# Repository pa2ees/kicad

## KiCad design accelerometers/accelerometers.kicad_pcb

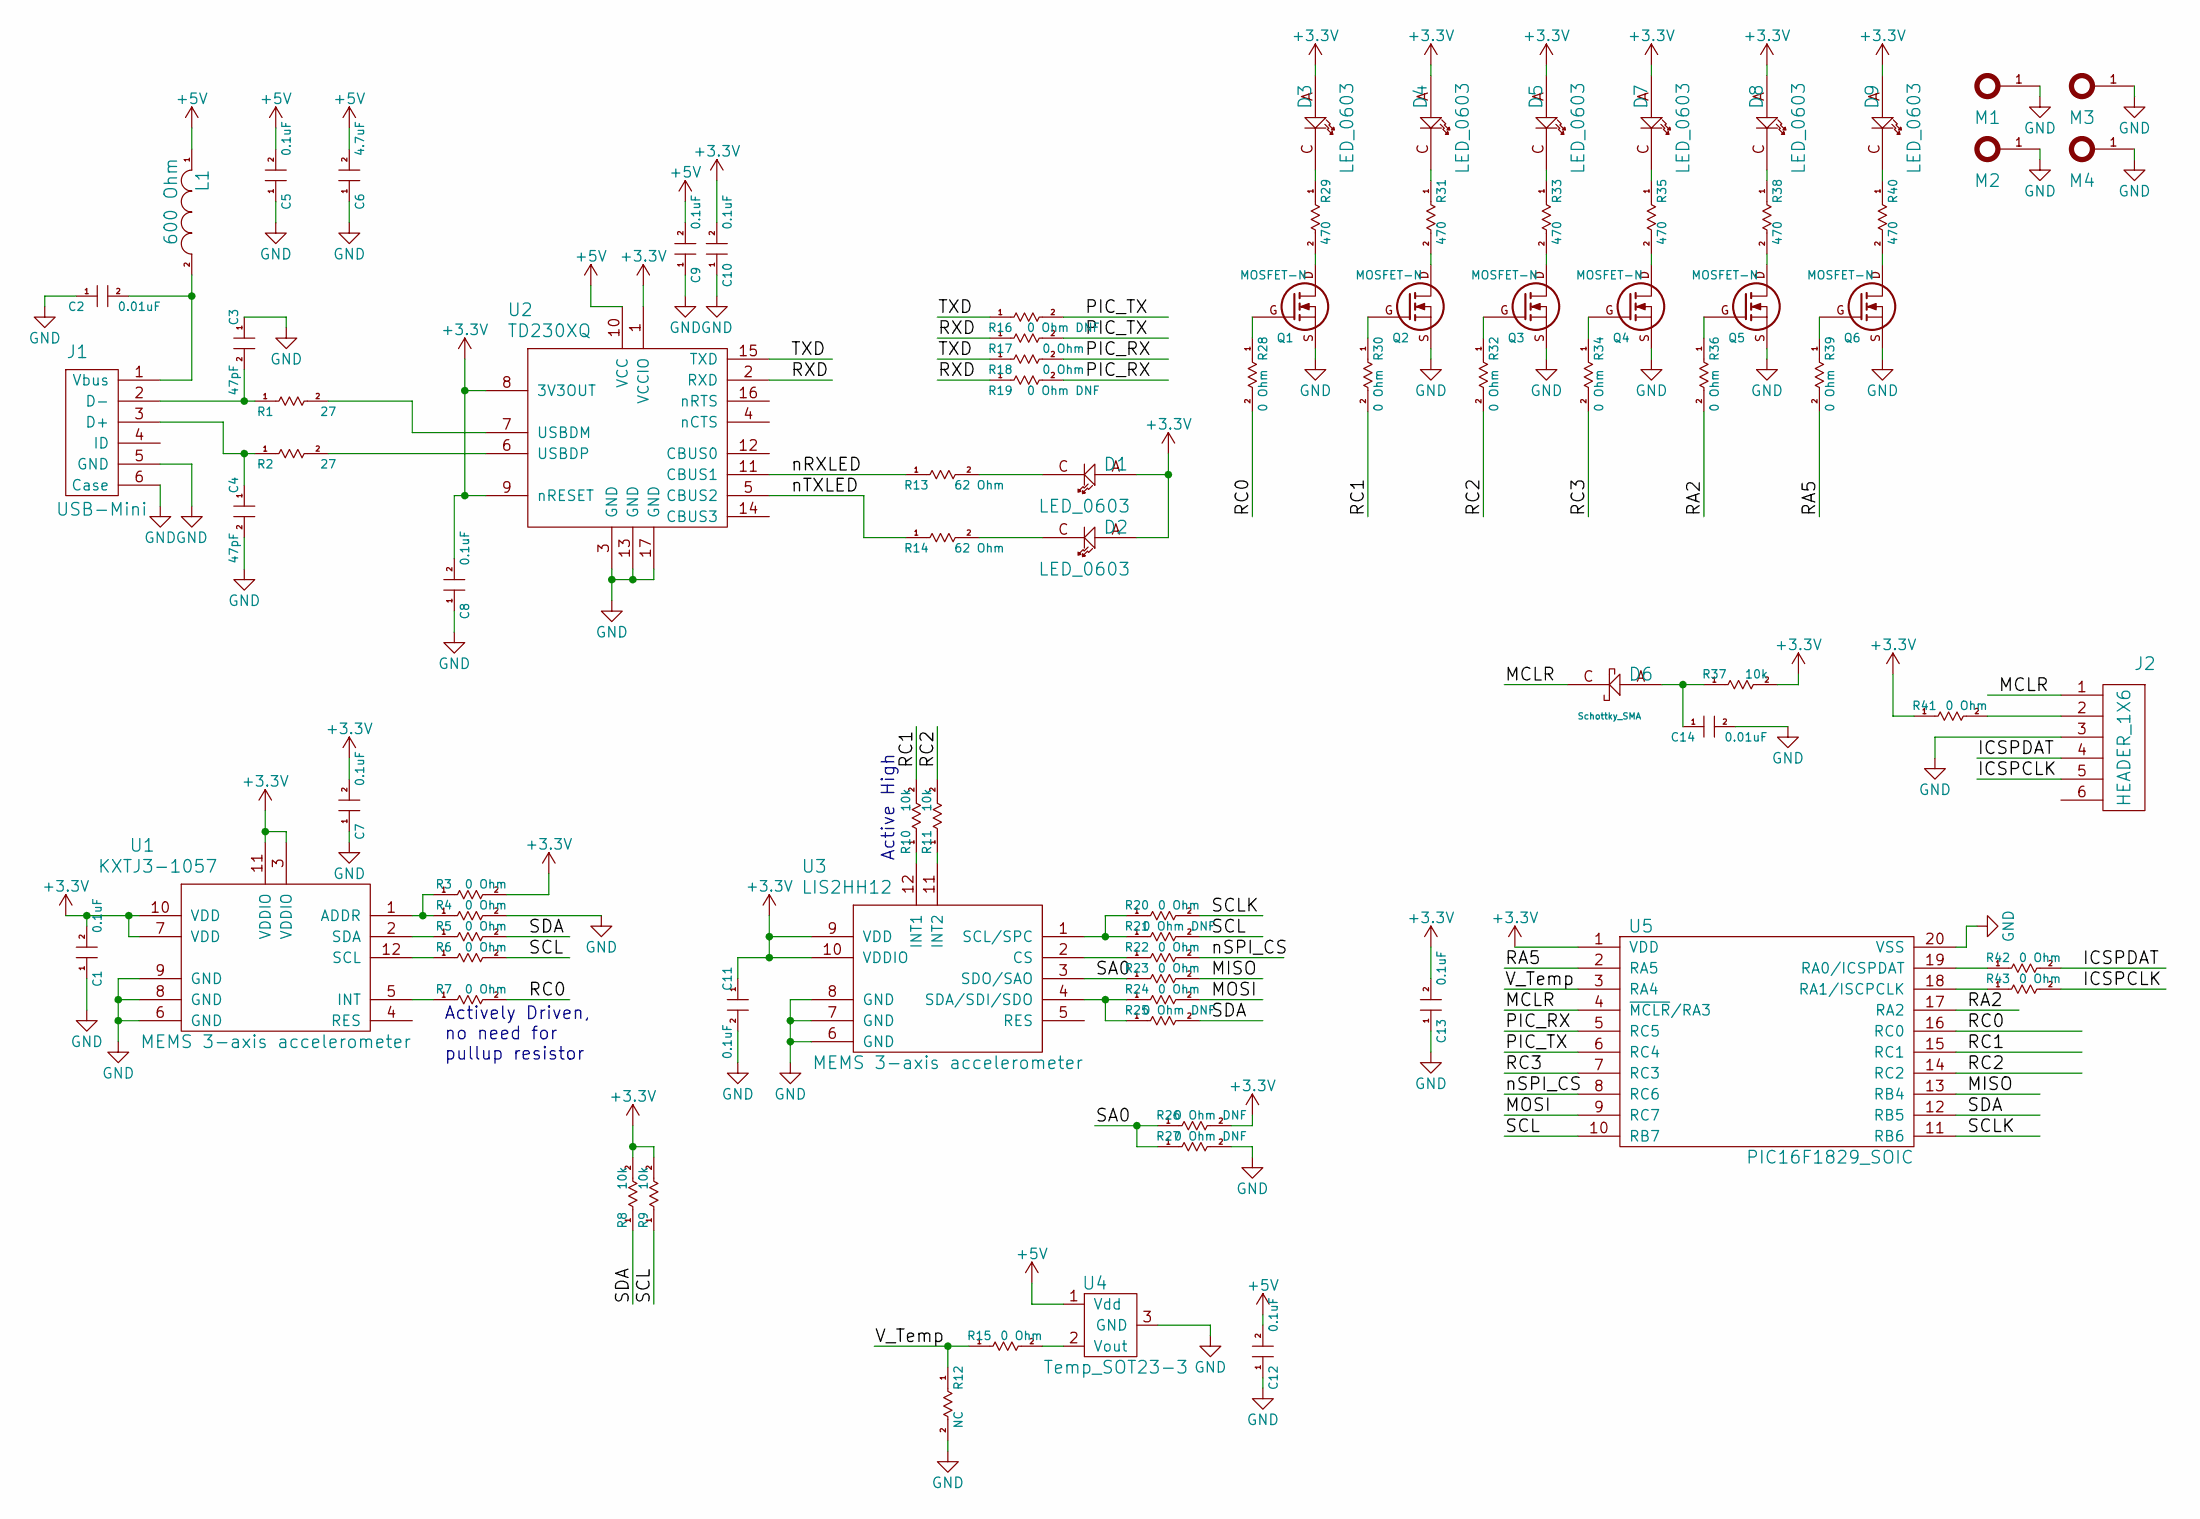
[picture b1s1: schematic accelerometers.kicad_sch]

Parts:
C1, C2, C3, C4, C5, C7, C8, C9, C10, C11: CAP_0603; C0603; MFG_PN {PN}
C6: CAP_0805; C0805; MFG_PN {PN}
C12, C13, C14: CAP_0603; C0603
D1, D2, D3, D4, D5, D7, D8, D9: LED_0603; D0603; MFG_PN LTST-C191KGKT
D6: Schottky_SMA; SMA; MFG_PN {PN}
J1: USB-Mini; MFG_PN 690-005-299-043
J2: HEADER_1X6; Header_6-pin_100mil
L1: IND; C0805; MFG_PN MI0805K601R-10
M1, M2, M3, M4: MNT-3MM; MNT-3mm
Q1, Q2, Q3, Q4, Q5, Q6: MOSFET-N; SOT-23-3-FET; MFG_PN 2N7002
R1, R2, R13, R14, R16, R17, R18, R19: RES_0603; R0603; MFG_PN {PN}
R3, R4, R5, R6, R7, R8, R9, R10, R11, R12, R15, R20, R21, R22, R23, R24, R25, R26, R27, R28, R30, R32, R34, R36, R37, R39, R41, R42, R43: RES_0603; R0603
R29, R31, R33, R35, R38, R40: RES_0603; R0603; MFG_PN RC0603JR-07470RL
U1: KXTJ3-1057; LGA12-2mm; MFG_PN KXTJ3-1057
U2: TD230XQ; QFN16-4mm; MFG_PN FT230XQ-R
U3: LIS2HH12; LGA12-2mm; MFG_PN LIS2HH12TR
U4: Temp_SOT23-3; SOT-23-3; MFG_PN MCP9700T
U5: PIC16F1829_SOIC; SO-20_300

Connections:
+3V3: C1.2, C7.2, C8.2, C10.2, C11.1, C13.2, D1.A, D2.A, D3.A, D4.A, D5.A, D7.A, D8.A, D9.A, R3.2, R8.2, R9.2, R26.2, R37.2, R41.1, U1.3 (VDDIO), U1.7 (VDD), U1.10 (VDD), U1.11 (VDDIO), U2.1 (VCCIO), U2.8 (3V3OUT), U2.9 (nRESET), U3.9 (VDD), U3.10 (VDDIO), U5.1 (VDD)
+5V: C5.2, C6.2, C9.2, C12.2, L1.1, U2.10 (VCC), U4.1 (Vdd)
/ICSPCLK: J2.5, R43.2
/ICSPDAT: J2.4, R42.2
/MCLR: D6.C, J2.1, U5.4 (~MCLR/RA3)
/MISO: R23.2, U5.13 (RB4)
/MOSI: R24.2, U5.9 (RC7)
/PIC_RX: R18.2, R19.2, U5.5 (RC5)
/PIC_TX: R16.2, R17.2, U5.6 (RC4)
/RA2: R36.2, U5.17 (RA2)
/RA5: R39.2, U5.2 (RA5)
/RC0: R7.2, R28.2, U5.16 (RC0)
/RC1: R10.2, R30.2, U5.15 (RC1)
/RC2: R11.2, R32.2, U5.14 (RC2)
/RC3: R34.2, U5.7 (RC3)
/RXD: R17.1, R19.1, U2.2 (RXD)
/SA0: R23.1, R26.1, R27.1, U3.3 (SDO/SAO)
/SCL: R6.2, R9.1, R21.2, U5.10 (RB7)
/SCLK: R20.2, U5.11 (RB6)
/SDA: R5.2, R8.1, R25.2, U5.12 (RB5)
/TXD: R16.1, R18.1, U2.15 (TXD)
/V_Temp: R12.1, R15.1, U5.3 (RA4)
/nRXLED: R13.1, U2.11 (CBUS1)
/nSPI_CS: R22.2, U5.8 (RC6)
/nTXLED: R14.1, U2.5 (CBUS2)
GND: C1.1, C2.1, C3.1, C4.2, C5.1, C6.1, C7.1, C8.1, C9.1, C10.1, C11.2, C12.1, C13.1, C14.2, J1.5 (GND), J1.6 (Case), J2.3, M1.1, M2.1, M3.1, M4.1, Q1.S, Q2.S, Q3.S, Q4.S, Q5.S, Q6.S, R4.2, R12.2, R27.2, U1.6 (GND), U1.8 (GND), U1.9 (GND), U2.3 (GND), U2.13 (GND), U2.17 (GND), U3.6 (GND), U3.7 (GND), U3.8 (GND), U4.3 (GND), U5.20 (VSS)
unnamed: C2.2, J1.1 (Vbus), L1.2
unnamed: C3.2, J1.2 (D-), R1.1
unnamed: C4.1, J1.3 (D+), R2.1
unnamed: C14.1, D6.A, R37.1
unnamed: D1.C, R13.2
unnamed: D2.C, R14.2
unnamed: D3.C, R29.1
unnamed: D4.C, R31.1
unnamed: D5.C, R33.1
unnamed: D7.C, R35.1
unnamed: D8.C, R38.1
unnamed: D9.C, R40.1
unnamed: J2.2, R41.2
unnamed: Q1.D, R29.2
unnamed: Q1.G, R28.1
unnamed: Q2.D, R31.2
unnamed: Q2.G, R30.1
unnamed: Q3.D, R33.2
unnamed: Q3.G, R32.1
unnamed: Q4.D, R35.2
unnamed: Q4.G, R34.1
unnamed: Q5.D, R38.2
unnamed: Q5.G, R36.1
unnamed: Q6.D, R40.2
unnamed: Q6.G, R39.1
unnamed: R1.2, U2.7 (USBDM)
unnamed: R2.2, U2.6 (USBDP)
unnamed: R3.1, R4.1, U1.1 (ADDR)
unnamed: R5.1, U1.2 (SDA)
unnamed: R6.1, U1.12 (SCL)
unnamed: R7.1, U1.5 (INT)
unnamed: R10.1, U3.12 (INT1)
unnamed: R11.1, U3.11 (INT2)
unnamed: R15.2, U4.2 (Vout)
unnamed: R20.1, R21.1, U3.1 (SCL/SPC)
unnamed: R22.1, U3.2 (CS)
unnamed: R24.1, R25.1, U3.4 (SDA/SDI/SDO)
unnamed: R42.1, U5.19 (RA0/ICSPDAT)
unnamed: R43.1, U5.18 (RA1/ISCPCLK)

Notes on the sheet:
Actively Driven, no need for pullup resistor
Active High

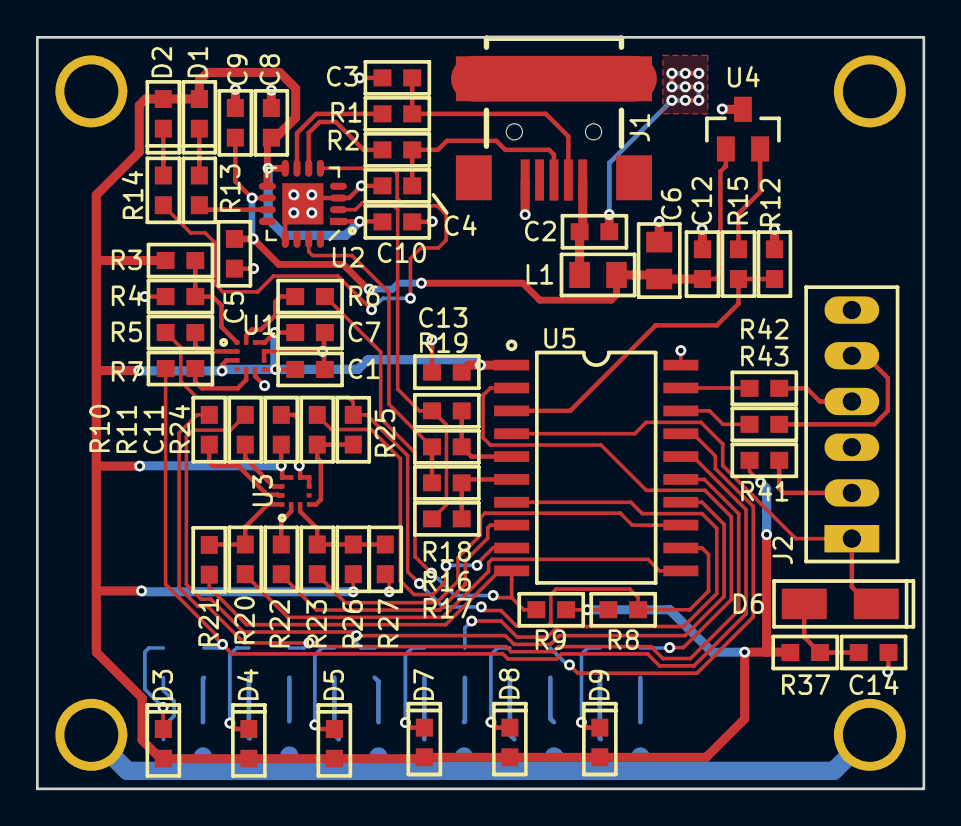
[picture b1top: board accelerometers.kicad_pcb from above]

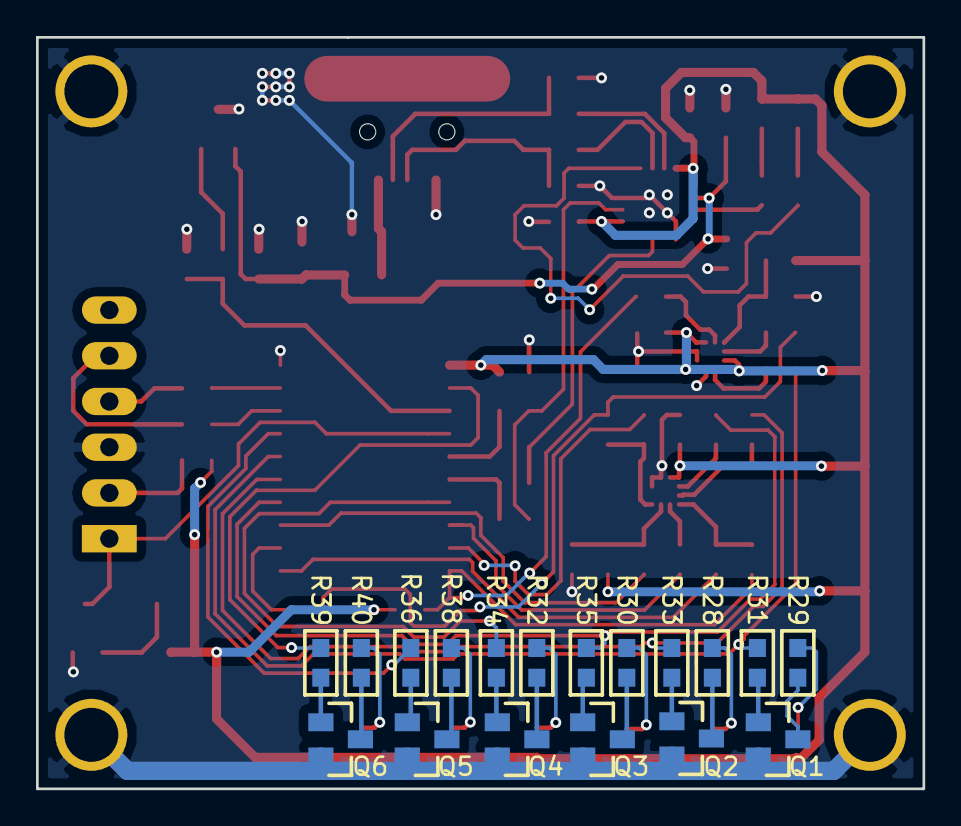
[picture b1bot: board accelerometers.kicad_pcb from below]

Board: 2 copper layers, 49.2 x 41.8 mm, 84 parts (18 on the bottom side), 65 nets.

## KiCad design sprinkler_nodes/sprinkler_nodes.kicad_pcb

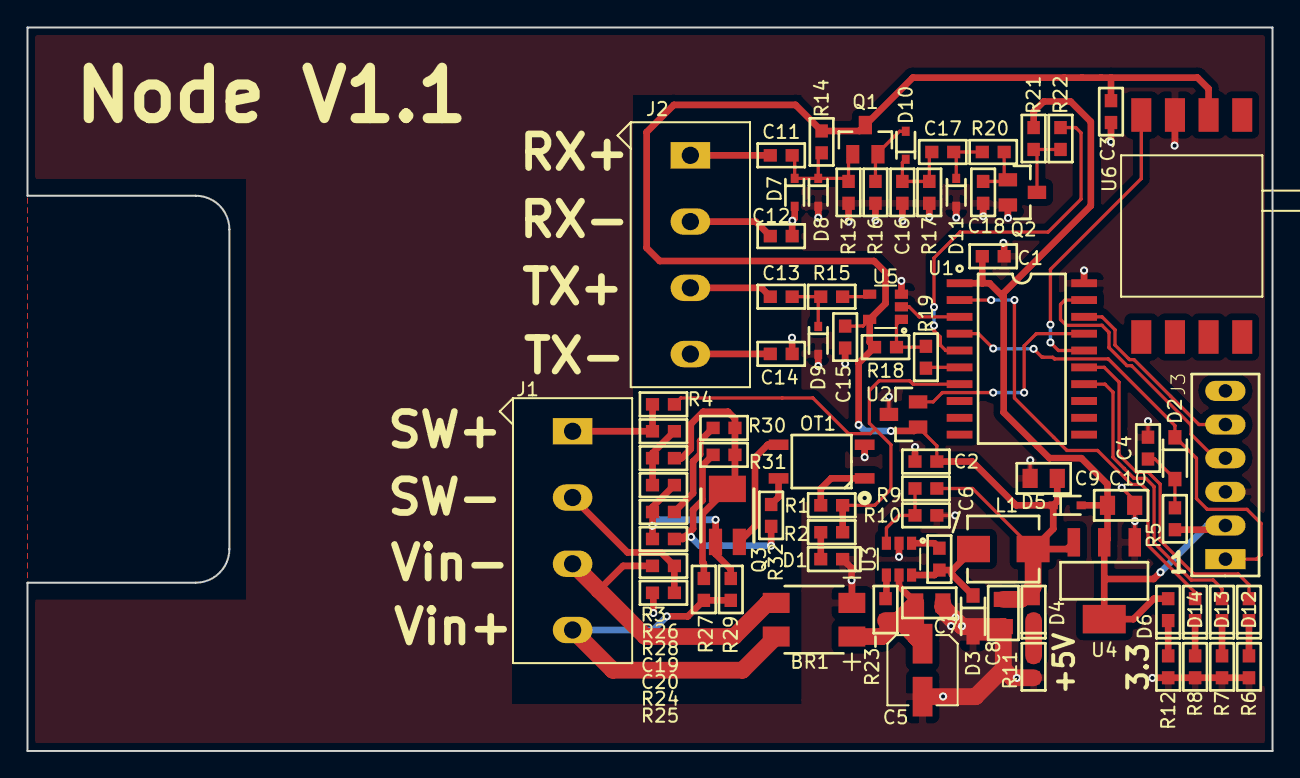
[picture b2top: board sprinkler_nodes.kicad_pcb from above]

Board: 2 copper layers, 94.0 x 54.6 mm, 81 parts (0 on the bottom side), 52 nets.

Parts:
BR1: MD5S_Diode_Bridge; MD5S
C1, C2, C3, C4, C6, C11, C12, C13, C14, C15, C16, C17, C18, C19, C20: CAP_0603; C0603
C5: CAP_ELEC; CAP_ELEC_5mm
C7, C8, C9, C10: CAP_0805; C0805
D1, D4, D6, D12, D13, D14: LED_0603; D0603
D2, D3: Schottky_SOD123; SOD123
D5, D10: Diode_SOD323; SOD323
D7, D9: Zener_SOD323; SOD323
D8, D11: Schottky_SOD323; SOD323
J1, J2: term_block_4-pin
J3: HEADER_1X6; Header_6-pin_100mil
L1: IND; PWR_IND_5.3x5
OT1: Opto-Triac-FODM30XX; FODM30XX
Q1, Q2: NPN; SOT-23-3
Q3: Triac; Triode SMB-3
R1, R2, R3, R4, R5, R6, R7, R8, R9, R10, R11, R12, R13, R14, R15, R16, R17, R18, R19, R20, R21, R22, R23, R24, R25, R26, R27, R28, R29, R30, R31, R32: RES_0603; R0603
U1: PIC16F1829_SOIC; SO-20_300
U2: Temp_SOT23-3; SOT-23-3
U3: MP2456; SOT-23-6
U4: TLV1117_3.3V; SOT-223
U5: NC7SZ125; SOT-23-5
U6: MPX5100

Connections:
+3V3: C1.2, C10.1, D5.A, D6.A, J3.2, R5.2, R21.1, U1.1, U4.2, U4.4
+5V: C2.2, C3.1, C8.1, C9.1, C15.1, D4.A, D5.C, L1.1, Q1.3, R9.1, R14.1, R18.1, U2.1, U4.3, U5.5, U6.2
/AN4: U1.16, U6.4
/CLKOUT: U1.3, U5.2
/GPIO1: D12.A, U1.15
/GPIO2: D13.A, U1.14
/GPIO3: D14.A, U1.2
/ICSPCLK: J3.5, U1.18
/ICSPDAT: J3.4, U1.19
/LOAD: R3.2, R26.1, R28.1
/MCLR: D2.C, J3.1, U1.4
/RF_IN: C11.1, J2.1
/RF_IN_RTN: C12.1, J2.2
/RF_OUT: C13.2, J2.3
/RF_OUT_RTN: C14.2, J2.4
/SW_1: R1.2, R2.2, R4.2, U1.7
/TRIAC_G: OT1.3, Q3.3
/UART_RX: R22.1, U1.5
/UART_TX: R19.2, U1.6
/VIN_AC: BR1.3, J1.4, R27.1, R29.1
/VIN_GND: BR1.2, J1.3, R24.2
/V_Temp: U1.17, U2.2
/power/EN: R23.2, U3.4
/power/VIN: BR1.4, C5.1, C7.1, R23.1, U3.5
GND: BR1.1, C1.1, C2.1, C3.2, C4.2, C5.2, C7.2, C8.2, C9.2, C10.2, C12.2, C14.1, C15.2, C16.2, C18.2, D1.C, D3.A, D7.A, D8.A, D9.A, D11.A, J3.3, OT1.2, Q2.2, R6.2, R7.2, R8.2, R10.2, R11.1, R12.1, R13.2, R16.2, R17.2, R25.2, U1.20, U2.3, U3.2, U4.1, U5.3, U6.3
unnamed: C4.1, D2.A, R5.1
unnamed: C6.1, U3.1
unnamed: C6.2, D3.C, L1.2, U3.6
unnamed: C11.2, D7.C, D8.C, Q1.1, R13.1, R14.2
unnamed: C13.1, D9.C, R15.1
unnamed: C16.1, C17.1, D10.C, R17.1
unnamed: C17.2, D11.C, R20.2
unnamed: C18.1, Q2.1, R20.1
unnamed: C19.1, R30.1
unnamed: C19.2, C20.2, Q3.1, R28.2, R29.2
unnamed: C20.1, R31.2, R32.1
unnamed: D1.A, R2.1
unnamed: D4.C, R11.2
unnamed: D6.C, R12.2
unnamed: D10.A, Q1.2, R16.1
unnamed: D12.C, R6.1
unnamed: D13.C, R7.1
unnamed: D14.C, R8.1
unnamed: J1.1, R3.1, R4.1
unnamed: J1.2, R24.1, R25.1
unnamed: OT1.1, R1.1
unnamed: OT1.4, R32.2
unnamed: Q2.3, R21.2, R22.2
unnamed: Q3.2, R26.2, R27.2, R30.2, R31.1
unnamed: R9.2, R10.1, U3.3
unnamed: R15.2, U5.4
unnamed: R18.2, R19.1, U5.1

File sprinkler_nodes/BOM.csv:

Part,Value,Designators,Manufacturer Part Number,Footprint,Part Value,Library
CAP_0603,.05uF,"C20, C19",{PN},C0603,CAP_0603,passives
CAP_0603,0.1uF,"C1, C4, C2, C15",,passives:C0603,CAP_0603,passives
CAP_0603,0.1uF,"C3, C6",{PN},C0603,CAP_0603,passives
CAP_0603,1uF,"C11, C17, C13, C14, C12",{PN},passives:C0603,CAP_0603,passives
CAP_0603,5nF,C16,{PN},passives:C0603,CAP_0603,passives
CAP_0603,80pF,C18,{PN},passives:C0603,CAP_0603,passives
CAP_0805,10uF,C8,{PN},C0805,CAP_0805,passives
CAP_0805,10uF,"C10, C9",,passives:C0805,CAP_0805,passives
CAP_0805,4.7uF,C7,{PN},C0805,CAP_0805,passives
CAP_ELEC,47uF,C5,UCM1H470MCL1GS,passives:CAP_ELEC_5mm,CAP_ELEC,passives
Diode_SOD323,,"D5, D10",BAS16HT1G,diodes:SOD323,Diode_SOD323,diodes
HEADER_1X6,,J3,,connectors:Header_6-pin_100mil,HEADER_1X6,connectors
IND,10uH,L1,CLF5030NIT-100M-D,passives:PWR_IND_5.3x5,IND,passives
LED_0603,,"D1, D12, D13, D14, D4, D6",LTST-C191KGKT,diodes:D0603,LED_0603,diodes
MD5S_Diode_Bridge,,BR1,MD5S,diodes:MD5S,MD5S_Diode_Bridge,diodes
MP2456,,U3,MP2456GJ,ICs:SOT-23-6,MP2456,regulators
MPX5100,,U6,MPXV5100DP,ICs:MPX5100,MPX5100,misc
NC7SZ125,,U5,NC7SZ125M5X,ICs:SOT-23-5,NC7SZ125,ICs
NPN,,"Q1, Q2",{PN},ICs:SOT-23-3,NPN,transistors
Opto-Triac-FODM30XX,,OT1,FODM3012-NF098,ICs:FODM30XX,Opto-Triac-FODM30XX,switches
PIC16F1829_SOIC,,U1,,ICs:SO-20_300,PIC16F1829_SOIC,microchip_mcu
RES_0603,0 Ohm,"R27, R26, R4, R3, R24, R25, R28, R29, R19",RC0603JR-07470RL,passives:R0603,RES_0603,passives
RES_0603,100k,"R14, R13",{PN},passives:R0603,RES_0603,passives
RES_0603,10k,"R5, R20, R18",,passives:R0603,RES_0603,passives
RES_0603,124k,R9,{PN},R0603,RES_0603,passives
RES_0603,1k,R22,{PN},passives:R0603,RES_0603,passives
RES_0603,23.7k,R10,{PN},R0603,RES_0603,passives
RES_0603,250,R17,{PN},passives:R0603,RES_0603,passives
RES_0603,280,R1,,passives:R0603,RES_0603,passives
RES_0603,39,R30,RC0603JR-07470RL,passives:R0603,RES_0603,passives
RES_0603,470,"R2, R6, R7, R8, R32, R31, R11, R12",RC0603JR-07470RL,passives:R0603,RES_0603,passives
RES_0603,50,R15,,passives:R0603,RES_0603,passives
RES_0603,500k,R23,{PN},R0603,RES_0603,passives
RES_0603,50k,R16,{PN},passives:R0603,RES_0603,passives
RES_0603,5k,R21,{PN},passives:R0603,RES_0603,passives
Schottky_SOD123,,"D2, D3",DFLS160-7,diodes:SOD123,Schottky_SOD123,diodes
Schottky_SOD323,,"D8, D11",NSR0530HT1G,diodes:SOD323,Schottky_SOD323,diodes
TLV1117_3.3V,,U4,TLV1117-33CDCYR,ICs:SOT-223,TLV1117_3.3V,regulators
Temp_SOT23-3,,U2,MCP9700T,ICs:SOT-23-3,Temp_SOT23-3,misc
Triac,,Q3,L4N3RP,ICs:Triode SMB-3,Triac,transistors
Zener_SOD323,,"D9, D7","DF2B7AE,H3F",diodes:SOD323,Zener_SOD323,diodes
term_block_4-pin,,"J1, J2",{PN},connectors:term_block_4-pin,term_block_4-pin,connectors

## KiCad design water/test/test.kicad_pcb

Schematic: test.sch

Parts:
C1, C2, C3, C4, C5, C6, C7, C8, C9, C10, C11, C12, C13, C14, C15, C16, C17, C18, C19, C20: CAP_0603; C0603
D1, D6, D8: Schottky_SMA; SMA; MFG_PN {PN}
D2, D3, D4, D5, D7: LED_0603; D0603; MFG_PN LTST-C191KGKT
J1: HEADER_1X6; Header_6-pin_100mil
J2, J3, J4, J5: term_block_4-pin; MFG_PN {PN}
M1, M2, M3, M4: MNT-3MM; MNT-3mm
Q1, Q2, Q3, Q4, Q5: MOSFET-N; SOT-23-3-FET; MFG_PN 2N7002
R1, R2, R3, R4, R5, R6, R7, R8, R9, R10, R11, R12, R13, R14, R15, R16, R17, R18, R22, R23, R24, R25, R26, R27, R28, R29, R30, R32, R33, R34, R35, R36, R37, R39, R46, R47, R48: RES_0603; R0603
R19, R20, R21, R31, R38: RES_0603; R0603; MFG_PN RC0603JR-07470RL
U1: MPX5100; MFG_PN MXP5100DP
U2: RS485_TRX_14pin; SO-14; MFG_PN SN65LBC180D
U3: PIC16F1829_SOIC; SO-20_300
U4, U5, U8, U9, U10, U11, U12: Level_Shifter_single; SOT-23-6; MFG_PN SN74LVC1T45DBVR
U6: Temp_SOT23-3; SOT-23-3; MFG_PN MCP9700T
U7: 23K256; SO-8; MFG_PN 23K256
U13, U14: Relay-EC2-5NU; EC2-5NU; MFG_PN EC2-5NU

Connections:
+3V3: C1.2, C5.1, C7.1, C9.2, C11.1, C13.1, C15.1, C17.1, C19.1, R5.2, R6.1, R16.2, R17.2, R24.2, R28.2, R29.2, R30.2, R33.2, R34.2, U3.1, U4.1, U5.1, U7.8, U8.1, U9.1, U10.1, U11.1, U12.1; also elsewhere on the board
+5V: C3.2, C4.2, C6.2, C8.2, C10.2, C12.2, C14.2, C16.2, C18.2, C20.2, D2.A, D3.A, D4.A, D5.A, D6.C, D7.A, D8.C, U1.2, U2.14, U4.6, U5.6, U6.1, U8.6, U9.6, U10.6, U11.6, U12.6, U13.1, U14.1; also elsewhere on the board
/Fill_SW: R32.2, U3.7
/GPIO: R37.1, U3.17, U11.3
/GPIO_5V: J4.3, R37.2, U11.4
/ICSPCLK: J1.5, R12.2
/ICSPDAT: J1.4, R11.2
/MCLR: D1.C, J1.1, U3.4
/MISO: R23.1, U3.13
/MOSI: R27.2, U3.9
/PIC_RX: R47.2, U3.5, U4.3
/PIC_RX_5V: R7.1, U4.4
/PIC_TX: R48.2, U3.6, U5.3
/PIC_TX_5V: R9.1, U5.4
/Pump_SW: R39.2, U3.14
/RX+: J2.1, R1.2, R4.1, U2.12
/RX-: J2.2, R1.1, R2.1, U2.11
/SCL: R36.1, U3.10, U12.3
/SCLK: R26.2, U3.11
/SCL_5V: J4.2, R36.2, U12.4
/SDA: R35.1, U3.12, U10.3
/SDA_5V: J4.1, R35.2, U10.4
/SW_24V_1: J3.1, U13.5
/SW_24V_2: J3.3, U13.8
/SW_24V_3: J5.1, U14.5
/TX+: J2.4, R3.2, R4.2, U2.9
/TX-: J2.3, R2.2, R3.1, U2.10
/TX_EN: R8.1, R13.1, U2.4, U9.4
/TX_EN_3V3: R46.2, U3.16, U9.3
/VIN_AC: J5.3, U13.4, U13.9, U14.4; also elsewhere on the board
/VIN_GND: J3.2, J3.4, J5.2, J5.4; also elsewhere on the board
/V_TankLevel: R10.2, R15.1, U3.3
/V_Temp: R18.1, R25.1, U3.2
/nRX_EN: R8.2, U2.3, U8.4
/nRX_EN_3V3: U3.15, U8.3
/nSPI_CS: R22.1, U3.8
GND: C1.1, C2.2, C3.1, C4.1, C5.2, C6.1, C7.2, C8.1, C9.1, C10.1, C11.2, C12.1, C13.2, C14.1, C15.2, C16.1, C17.2, C18.1, C19.2, C20.1, J1.3, J4.4, M1.1, M2.1, M3.1, M4.1, Q1.S, Q2.S, Q3.S, Q4.S, Q5.S, R13.2, R14.2, R15.2, R25.2, U1.3, U2.7, U3.20, U4.2, U5.2, U6.3, U7.4, U8.2, U9.2, U10.2, U11.2, U12.2; also elsewhere on the board
unnamed: C2.1, D1.A, R5.1
unnamed: D2.C, R19.1
unnamed: D3.C, R20.1
unnamed: D4.C, R21.1
unnamed: D5.C, R31.2
unnamed: D6.A, Q4.D, R31.1, U13.12
unnamed: D7.C, R38.2
unnamed: D8.A, Q5.D, R38.1, U14.12
unnamed: J1.2, R6.2
unnamed: Q1.D, R19.2
unnamed: Q1.G, R46.1
unnamed: Q2.D, R20.2
unnamed: Q2.G, R47.1
unnamed: Q3.D, R21.2
unnamed: Q3.G, R48.1
unnamed: Q4.G, R32.1
unnamed: Q5.G, R39.1
unnamed: R7.2, U2.2
unnamed: R9.2, U2.5
unnamed: R10.1, U1.4
unnamed: R11.1, U3.19
unnamed: R12.1, U3.18
unnamed: R14.1, U2.6
unnamed: R16.1, U4.5
unnamed: R17.1, U5.5
unnamed: R18.2, U6.2
unnamed: R22.2, U7.1
unnamed: R23.2, U7.2
unnamed: R24.1, U7.7
unnamed: R26.1, U7.6
unnamed: R27.1, U7.5
unnamed: R28.1, U8.5
unnamed: R29.1, U9.5
unnamed: R30.1, U10.5
unnamed: R33.1, U11.5
unnamed: R34.1, U12.5

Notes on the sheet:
Termination Resistors
Half Duplex Connections
RA5 is not analog

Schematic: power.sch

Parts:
C21: CAP_ELEC; CAP_ELEC_5mm; MFG_PN EEE-1AA101WR
C22, C23: CAP_0805; C0805
C24: CAP_0603; C0603; MFG_PN {PN}
C25: CAP_ELEC; CAP_ELEC_10mm; MFG_PN EEE-1EA471P
C26: CAP_ELEC; CAP_ELEC_10mm; MFG_PN EEE-FK1J101P
D9, D13, D14, D15, D16: Diode_SMB; SMB; MFG_PN {PN}
D10, D11: LED_0603; D0603; MFG_PN LTST-C191KGKT
D12: Schottky_SMA; SMA; MFG_PN 1N5819HW-7-F
L1: IND; SRR1260-221K; MFG_PN SRR1260-221K
R40, R45: RES_0805; R0805; MFG_PN {PN}
R41, R42: RES_0603; R0603; MFG_PN RC0603JR-07470RL
R43, R44: RES_0603; R0603; MFG_PN {PN}
U15: MC34063A_buck; SO-8; MFG_PN MC34063A
U16: TLV1117_3.3V; SOT-223

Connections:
+3V3: C21.1, C23.1, D9.A, D10.A, U16.2 (Vout), U16.4 (Tab); also elsewhere on the board
+5V: C22.1, C25.1, D9.C, D11.A, L1.2, R43.1, U16.3 (Vin); also elsewhere on the board
/VIN_AC: D13.A, D14.C; also elsewhere on the board
/VIN_GND: D15.A, D16.C, R45.1; also elsewhere on the board
/power/VIN: C26.1, D13.C, D15.C, R40.1, U15.6 (Vcc)
GND: C21.2, C22.2, C23.2, C24.2, C25.2, C26.2, D12.A, D14.A, D16.A, R41.1, R42.1, R44.1, R45.2, U15.4 (GND), U16.1 (GND); also elsewhere on the board
unnamed: C24.1, U15.3 (Ct)
unnamed: D10.C, R42.2
unnamed: D11.C, R41.2
unnamed: D12.C, L1.1, U15.2 (SWe)
unnamed: R40.2, U15.1 (SWc), U15.7 (Ipk), U15.8 (Drive)
unnamed: R43.2, R44.2, U15.5 (Comp)

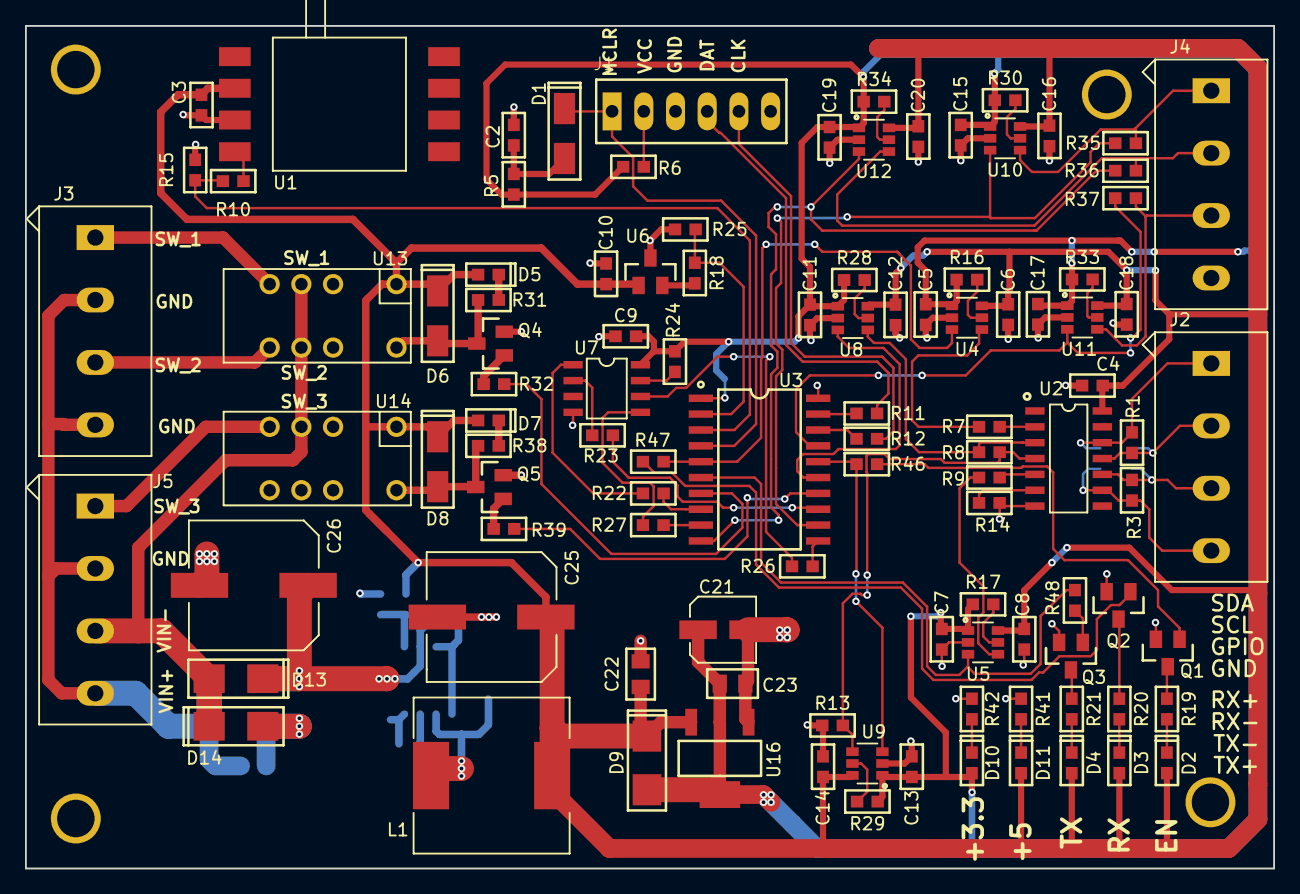
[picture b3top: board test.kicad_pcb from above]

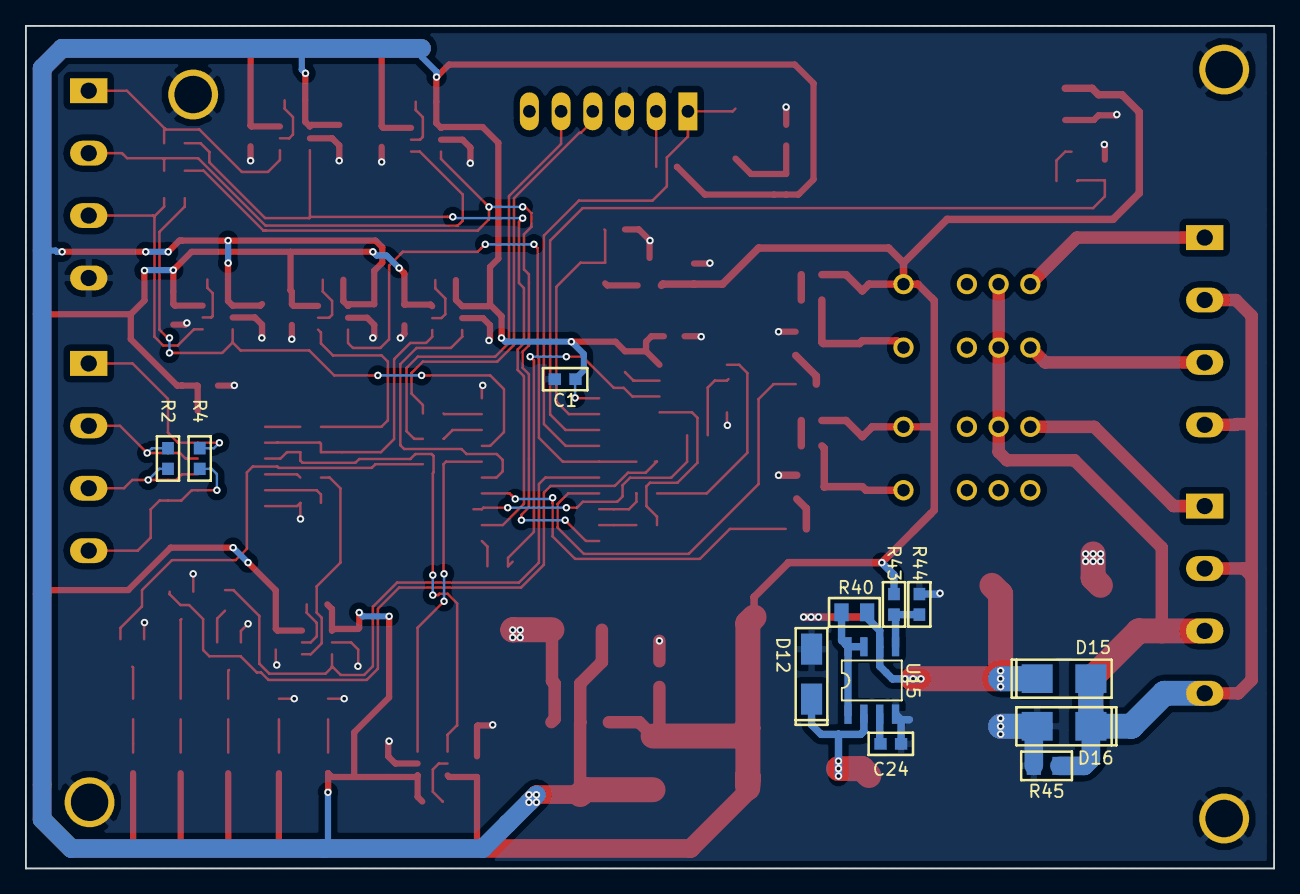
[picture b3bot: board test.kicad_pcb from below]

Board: 2 copper layers, 100.0 x 67.5 mm, 121 parts (12 on the bottom side), 80 nets.

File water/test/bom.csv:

Part,Value,Designators,Manufacturer Part Number,Manufacturer 2 Part Number,Footprint,Part Value,Library
23K256,,U7,23K256,N25S830HA,ICs:SO-8,23K256,diodes
CAP_0603,0.1uF,"C3, C1, C4, C2, C9, C10, C5, C6, C7, C8, C11, C12, C13, C14, C15, C16, C17, C18, C19, C20",,,passives:C0603,CAP_0603,passives
CAP_0603,100pF,C24,{PN},,passives:C0603,CAP_0603,passives
CAP_0805,10uF,"C23, C22",,,passives:C0805,CAP_0805,passives
CAP_ELEC,100uF,C21,EEE-1AA101WR,,passives:CAP_ELEC_5mm,CAP_ELEC,passives
CAP_ELEC,100uF,C26,EEE-FK1J101P,,passives:CAP_ELEC_10mm,CAP_ELEC,passives
CAP_ELEC,470uF,C25,EEE-1EA471P,,passives:CAP_ELEC_10mm,CAP_ELEC,passives
Diode_SMB,,"D13, D15, D14, D16, D9",{PN},,diodes:SMB,Diode_SMB,diodes
HEADER_1X6,,J1,,,connectors:Header_6-pin_100mil,HEADER_1X6,connectors
IND,220nH,L1,SRR1260-221K,,passives:SRR1260-221K,IND,passives
LED_0603,,"D4, D3, D2, D5, D7, D11, D10",LTST-C191KGKT,,diodes:D0603,LED_0603,diodes
Level_Shifter_single,,"U4, U5, U8, U9, U11, U10, U12",SN74LVC1T45DBVR,,ICs:SOT-23-6,Level_Shifter_single,IC_Interface
MC34063A_buck,,U15,MC34063A,,ICs:SO-8,MC34063A_buck,regulators
MNT-3MM,,"M1, M3, M2, M4",,,mechanical:MNT-3mm,MNT-3MM,mechanical
MOSFET-N,,"Q3, Q2, Q1, Q4, Q5",2N7002,,ICs:SOT-23-3-FET,MOSFET-N,transistors
MPX5100,,U1,MXP5100DP,,ICs:MPX5100,MPX5100,misc
PIC16F1829_SOIC,,U3,,,ICs:SO-20_300,PIC16F1829_SOIC,microchip_mcu
RES_0603,0 Ohm,"R11, R12, R8, R7, R9, R14, R2, R4, R6, R18, R10, R46, R47, R48",,,passives:R0603,RES_0603,passives
RES_0603,1.2k,R44,{PN},,passives:R0603,RES_0603,passives
RES_0603,100,"R26, R27, R23, R22, R32, R39",,,passives:R0603,RES_0603,passives
RES_0603,10k,"R13, R5, R24, R16, R17, R28, R29, R30, R33, R34",,,passives:R0603,RES_0603,passives
RES_0603,3.6k,R43,{PN},,passives:R0603,RES_0603,passives
RES_0603,470,"R21, R20, R19, R31, R38, R41, R42",RC0603JR-07470RL,,passives:R0603,RES_0603,passives
RES_0603,75,"R1, R3",,,passives:R0603,RES_0603,passives
RES_0603,NC,"R25, R15, R35, R36, R37",,,passives:R0603,RES_0603,passives
RES_0805,0.75,R40,{PN},,R0805,RES_0805,passives
RES_0805,NC,R45,{PN},,passives:R0805,RES_0805,passives
RS485_TRX_14pin,,U2,SN65LBC180D,ISL8489E,ICs:SO-14,RS485_TRX_14pin,IC_Interface
Relay-EC2-5NU,,"U13, U14",EC2-5NU,,switches:EC2-5NU,Relay-EC2-5NU,switches
Schottky_SMA,,"D1, D6, D8, D12",{PN},,diodes:SMA,Schottky_SMA,diodes
TLV1117_3.3V,,U16,,,ICs:SOT-223,TLV1117_3.3V,regulators
Temp_SOT23-3,,U6,MCP9700T,,ICs:SOT-23-3,Temp_SOT23-3,misc
term_block_4-pin,,"J3, J5, J4, J2",{PN},,connectors:term_block_4-pin,term_block_4-pin,connectors

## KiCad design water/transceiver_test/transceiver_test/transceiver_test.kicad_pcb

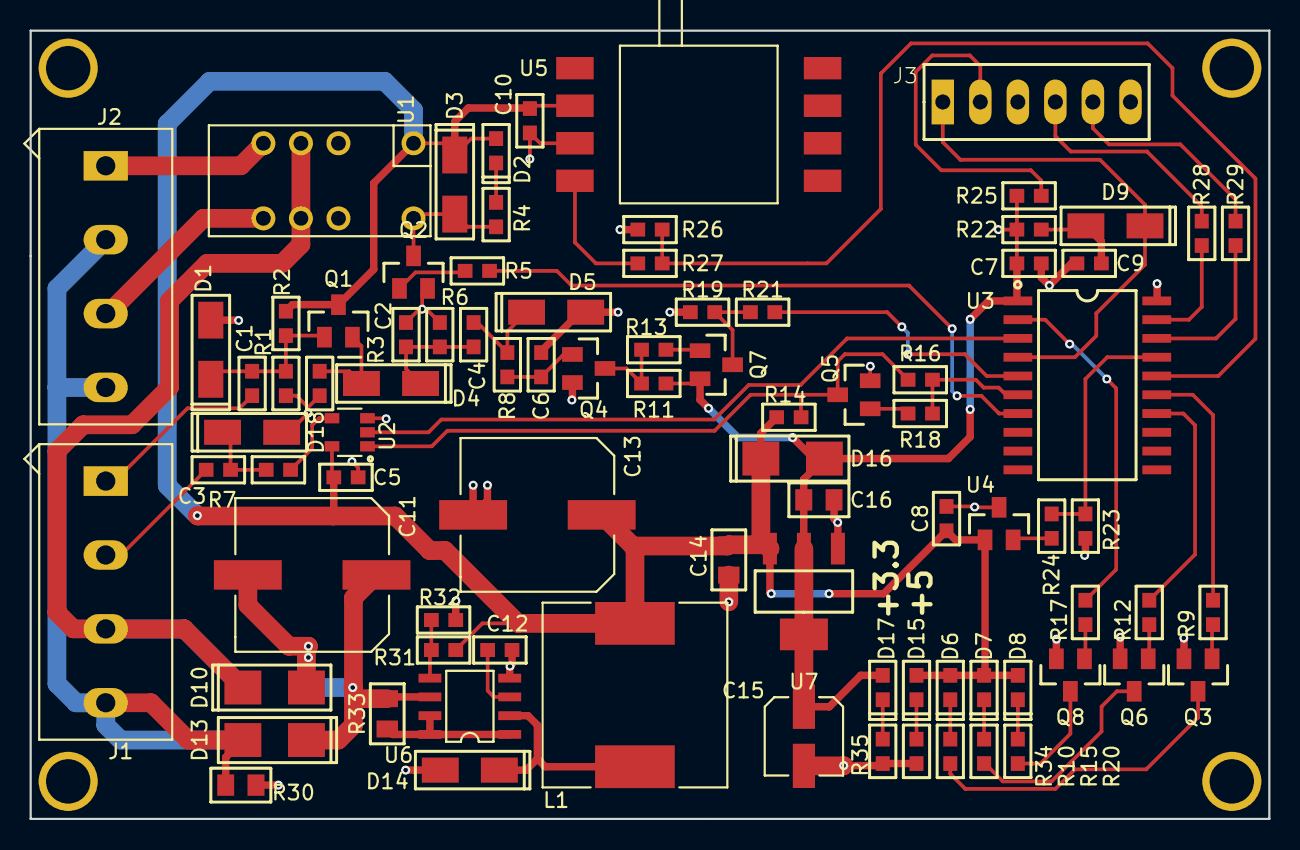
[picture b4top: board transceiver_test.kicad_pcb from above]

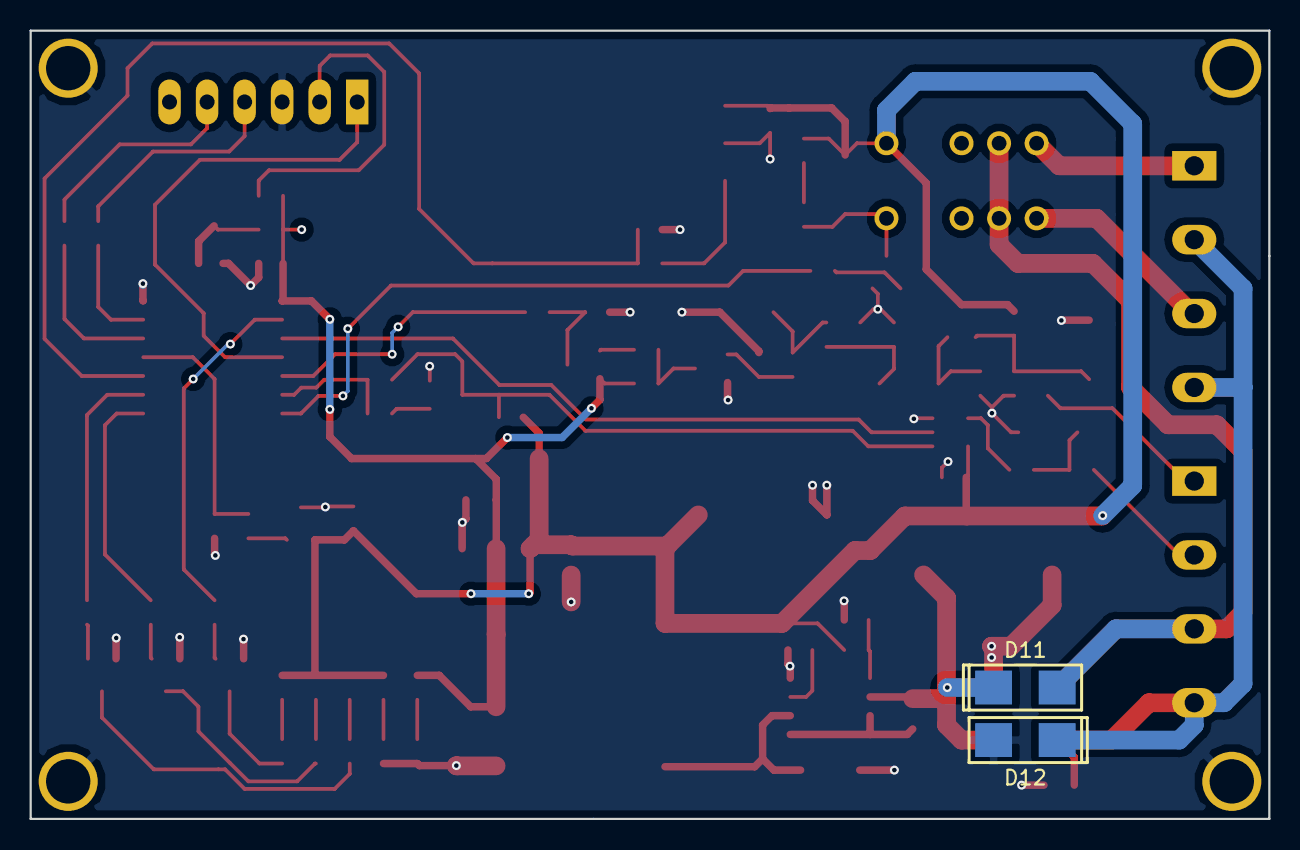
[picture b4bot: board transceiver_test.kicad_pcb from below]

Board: 2 copper layers, 83.8 x 53.3 mm, 92 parts (2 on the bottom side), 58 nets.

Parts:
C1, C2, C3, C4, C5, C6, C7, C8, C9, C10, C12: CAP_0603; C0603
C11, C13: CAP_ELEC; CAP_ELEC_10mm
C14, C16: CAP_0805; C0805
C15: CAP_ELEC; CAP_ELEC_5mm
D1, D18: Zener_SMA; SMA
D2, D6, D7, D8, D15, D17: LED_0603; D0603
D3, D9, D14: Schottky_SMA; SMA
D4, D5: Diode_SMA; SMA
D10, D11, D12, D13, D16: Diode_SMB; SMB
J1, J2: term_block_4-pin
J3: HEADER_1X6; Header_6-pin_100mil
L1: IND; SRR1260-221K
M1, M2, M3, M4: MNT-3MM; MNT-3mm
Q1, Q4, Q5: NPN; SOT-23-3
Q2, Q3, Q6, Q8: MOSFET-N; SOT-23-3-FET
Q7: PNP; SOT-23-3
R1, R2, R3, R4, R5, R6, R7, R8, R9, R10, R11, R12, R13, R14, R15, R16, R17, R18, R19, R20, R21, R22, R23, R24, R25, R26, R27, R28, R29, R31, R32, R34, R35: RES_0603; R0603
R30, R33: RES_0805; R0805
U1: Relay-EC2-5NU; EC2-5NU
U2: NC7SZ125; SOT-23-5
U3: PIC16F1829_SOIC; SO-20_300
U4: Temp_SOT23-3; SOT-23-3
U5: MPX5100
U6: MC34063A_buck; SO-8
U7: TLV1117_3.3V; SOT-223

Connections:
+3V3: C7.2, C15.1, C16.1, D16.A, D17.A, Q7.2, R11.1, R22.2, R25.1, U3.1, U7.2, U7.4
+5V: C5.1, C8.2, C10.2, C13.1, C14.1, D2.A, D3.C, D6.A, D7.A, D8.A, D15.A, D16.C, L1.2, Q1.3, R2.1, R14.1, R31.1, U1.1, U2.5, U4.1, U5.2, U7.3
/AN4: R26.2, R27.1, U3.16
/CLKOUT: U2.2, U3.3
/GPIO1: R9.2, U3.15
/GPIO2: R12.2, U3.14
/GPIO3: R17.2, U3.2
/ICSPCLK: J3.5, R29.2
/ICSPDAT: J3.4, R28.2
/MCLR: D9.C, J3.1, U3.4
/Power/VIN: C11.1, D11.C, D13.C, R33.1, U6.6
/RF_IN: C1.1, J1.1
/RF_OUT: C3.2, J1.2
/SW_1: R5.2, U3.7
/SW_24V_1: J2.1, U1.5
/SW_24V_2: J2.3, U1.8
/UART_RX: R21.1, U3.5
/UART_TX: R16.2, R18.2, U3.6
/VIN_AC: D10.C, D11.A, J1.3, U1.4, U1.9
/VIN_GND: D12.C, D13.A, J1.4, J2.2, J2.4, R30.1
/V_Temp: R23.1, R24.1, U3.17
GND: C2.2, C5.2, C6.2, C7.1, C8.1, C9.2, C10.1, C11.2, C12.2, C13.2, C14.2, C15.2, C16.2, D1.A, D5.A, D10.A, D12.A, D14.A, D18.A, J3.3, M1.1, M2.1, M3.1, M4.1, Q2.S, Q3.S, Q4.2, Q5.2, Q6.S, Q8.S, R1.2, R3.2, R6.2, R19.2, R23.2, R27.2, R30.2, R32.1, R34.1, R35.1, U2.3, U3.20, U4.3, U5.3, U6.4, U7.1
unnamed: C1.2, D1.C, Q1.1, R1.1, R2.2
unnamed: C2.1, C4.1, D4.C, R6.1
unnamed: C3.1, D18.C, R7.1
unnamed: C4.2, D5.C, R8.2
unnamed: C6.1, Q4.1, R8.1
unnamed: C9.1, D9.A, R22.1
unnamed: C12.1, U6.3
unnamed: D2.C, R4.2
unnamed: D3.A, Q2.D, R4.1, U1.12
unnamed: D4.A, Q1.2, R3.1
unnamed: D6.C, R10.1
unnamed: D7.C, R15.1
unnamed: D8.C, R20.1
unnamed: D14.C, L1.1, U6.2
unnamed: D15.C, R34.2
unnamed: D17.C, R35.2
unnamed: J3.2, R25.2
unnamed: Q2.G, R5.1
unnamed: Q3.D, R10.2
unnamed: Q3.G, R9.1
unnamed: Q4.3, R11.2, R13.2
unnamed: Q5.1, R18.1
unnamed: Q5.3, R14.2, R16.1, U2.1
unnamed: Q6.D, R15.2
unnamed: Q6.G, R12.1
unnamed: Q7.1, R13.1
unnamed: Q7.3, R19.1, R21.2
unnamed: Q8.D, R20.2
unnamed: Q8.G, R17.1
unnamed: R7.2, U2.4
unnamed: R24.2, U4.2
unnamed: R26.1, U5.4
unnamed: R28.1, U3.19
unnamed: R29.1, U3.18
unnamed: R31.2, R32.2, U6.5
unnamed: R33.2, U6.1, U6.7, U6.8
